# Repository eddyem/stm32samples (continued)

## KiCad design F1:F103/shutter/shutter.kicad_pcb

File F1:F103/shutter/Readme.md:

Shutter control 
===============

Works with bi-stable shutter. 
You can find the device in `/dev/shutterX` (symlink to `/dev/ttyUSBX`).

After powered on, the device will try to close shutter (during one second). 

The CCD (or manual) controlled input allows to open/close shutter by changing its level (depending on `ccdactive` parameter). 
If current configuration can't open or close the shutter immediately, it will be opened/closed as soon as possible, while the input holds its level.

When the shutter is closed, the device will send over USB a message like
```
exptime=10000
shutter=closed
```
with calculated value of opened time and current shutter state. 
If the error occured and shutter can't be closed, user will read `exp=cantclose`, shutter will come into error state. You should close the shutter by external command in that case.

After the shutter completely opened, user can read a message `shutter=opened`.

## Pinout

**PB0** (pullup in) - hall (or reed switch) sensor input (active low) - opened shutter detector

**PB11** (pullup in) - CCD or button input: open at low signal, close at high

**PA3** (ADC in) - shutter voltage (approx 1/12 U)

**PA5** (PP out) - TLE5205 IN2

**PA6** (PP out) - TLE5205 IN1

**PA7** (pullup in) - TLE5205 FB

**PA10** (PP out) - USB pullup (active low)

**PA11**, **PA12** - USB

**PA13**, **PA14** - SWD

## Commands

###    debugging options:
* '0' - shutter OPE
* '1' - shutter CLO
* '2' - shutter OFF
* '3' - shutter HIZ
* 'W' - test watchdog

###    configuration:
* '< n' - voltage on discharged capacitor (*100)
* '> n' - voltage on fully charged capacitor (*100)
* '# n' - duration of electrical pulse to open/close shutter (ms)
* '$ n' - duration of mechanical work to completely open/close shutter (ms)
* '* n' - shutter voltage multiplier
* '/ n' - shutter voltage divider (V=Vadc*M/D)
* 'c n' - open shutter when CCD ext level is n (0/1)
* 'd' - dump current config
* 'e' - erase flash storage
* 'h n' - shutter is opened when hall level is n (0/1)
* 's' - save configuration into flash

###    common control:
* 'A' - get raw ADC values
* 'C' - close shutter / abort exposition
* 'E n' - expose for n milliseconds
* 'O' - open shutter
* 'R' - software reset
* 'S' - get shutter state; also hall and ccd inputs state (1 - active)
* 't' - get MCU temperature (/10degC)
* 'T' - get Tms
* 'v' - get Vdd (/100V)
* 'V' - get shutter voltage (/100V)

Any wrong long message will echo back. Any wrong short command will show help list.

## Shutter control
Commands '0' ...  '3' should be used only for debugging purposes.
To open/close shutter use only 'O', 'C' and 'E' commands.

When opening or closing shutter you will first receive an answer: `OK` if command could be done or `ERR` if there's insufficient voltage on capacitor or shutter is absent.
After opened the message `shutter=opened` will appear. After closing you will receive messages `exptime=xxx` (when `xxx` is approx. exp. time in milliseconds) and `shutter=closed`.

Command 'E' could return `OK`, `ERR` or `ERRNUM`/`I32OVERFLOW` in wrong number format (number could be decimal, 0x.. - hexadecimal, b.. - binary or 0.. - octal).
"Status" command in this case will return `shutter=exposing` and `expfor=xxx` - the given exposition time.

When exposition starts you will receive message `OK` and `shutter=opened`. After its end you'll got `exptime=...`, `shutter=closed`.
If shutter can't be closed, you will give a lots of `exp=cantclose` and different error messages until problem be solved. To stop this error messages give command 'O'.

## Different commands
* 'A' will show raw values for all ADC channels: 0. - capacitor voltage, 1 - MCU temperature, 2 - MCU Vdd. You will give messages like `adcX=val`.

* 't' - `mcut=val`, where val = T*10 degrC.

* 'T' - `tms=val`, val in ms.

* 'v' - `vdd=val`, val in V*100

* 'V' - `voltage=val`, val in V*100

* 'S' - several answers:
  * `shutter=`: `closed`, `opened`, `error`, `process`, `wait` or `exposing` - shutter state 
  * `expfor=...` (only when exposing by command Exxx) - show given exposition time
  * `exptime=...` (only when shutter is opened) - show time since opening
  * `regstate=`: `open`, `close`, `off` or `hiZ` - TLE5205 outputs state
  * `fbstate=`: `0` or `1` - TLE5205 FB out state (1 - error: insufficient voltage or shutter absent)
  * `hall=`: `0` or `1` - 1 for opened shutter, 0 for closed
  * `ccd=`: `0` or `1` - 1 for active (closed contacts) state of "CCD" input

## Configuration
All configuration stored in MCU flash memory, to dump current config just enter command 'd' and you will give an answer like
```
userconf_sz=16
ccdactive=1
hallactive=0
minvoltage=400
workvoltage=700
shuttertime=20
waitingtime=30
shtrvmul=143
shtrvdiv=25
```

* `userconf_sz` - "magick" number to determine first non-empty record in flash storage. The aligned size of one record in bytes.
* `ccdactive` - is level of 'CCD' input to open shutter (1 to open on high and 0 to open on low signal), change this value with command `c`.
* `hallactive` - the same for Hall sensor or reed switch mounted on shutter to indicate opened state, change with `h`.
* `minvoltage` - voltage level on discharged capacitor (V*100 Volts), when shutter is in opened/closed state, the power will be off from coils reaching this level. Can be from 1V to 10V. Change with `<`.
* `workvoltage` - minimal level (V*100 Volts) of charged capacitor to start process of opening/closing, you can open/close shutter only with higher voltage. Can be from 5V to 100V. Change with `>`.
* `shuttertime` - maximal time (milliseconds) of holding active voltage on shutter's coils. Can be from 5ms to 1s. Change with `#`.
* `waitingtime` - waiting time for the shutter to finish its job. The expose time can't be less than this value. Can be from 5ms to 1s. Change with `$`.
* `shtrvmul` - multiplier to calculate capacitor voltage from voltage on ADC input of MCU. Vcap = V*shtrvmul/shtrvdiv. Can be from 1 to 65535. Change with `*`.
* `shtrvdiv` - divider of capacitor voltage calculation. Can be from 1 to 65535. Change with `/`.

All changes of configuration processed in RAM and acts immediately after changed. If you want to store changes, use command `s`.

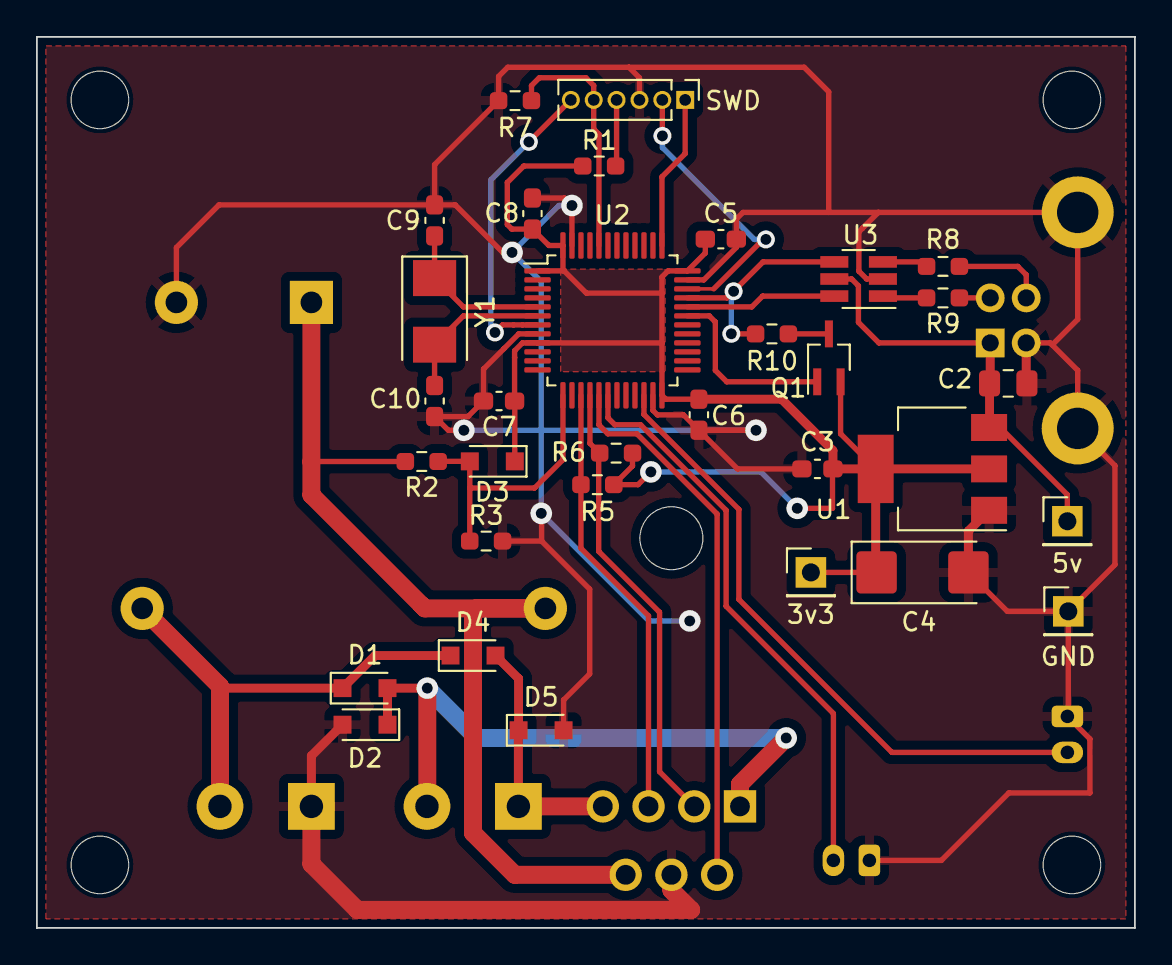
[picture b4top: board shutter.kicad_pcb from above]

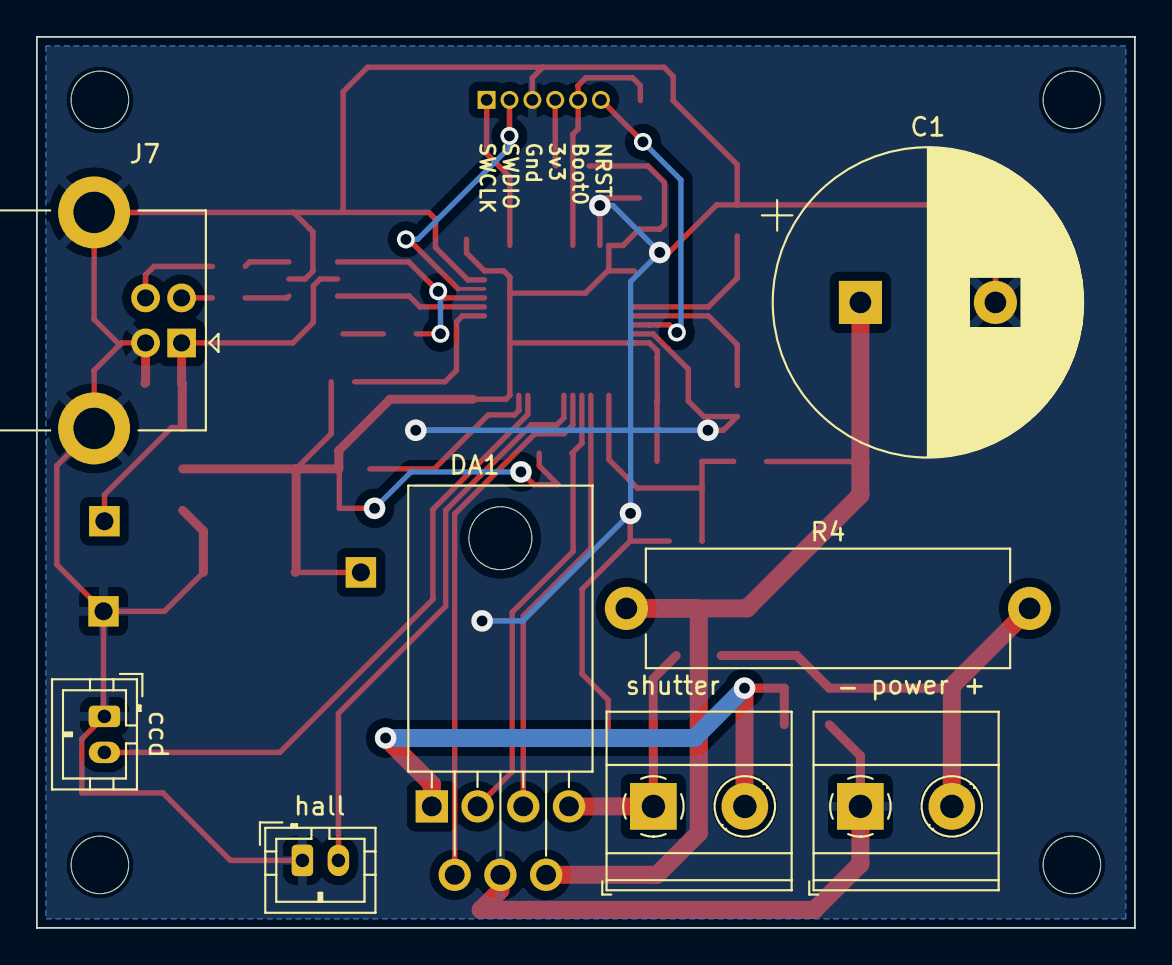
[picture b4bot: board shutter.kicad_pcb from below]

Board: 2 copper layers, 61.0 x 49.5 mm, 44 parts (8 on the bottom side), 28 nets.

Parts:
C1: 2200u, 40V; CP_Radial_D17.0mm_P7.50mm
C2: 1u; C_0805_2012Metric_Pad1.18x1.45mm_HandSolder
C3, C5, C6, C7, C8: 0.1; C_0603_1608Metric_Pad1.08x0.95mm_HandSolder
C4: 47u; CP_EIA-6032-28_Kemet-C_Pad2.25x2.35mm_HandSolder
C9, C10: 6; C_0603_1608Metric_Pad1.08x0.95mm_HandSolder
D1, D2, D3, D4, D5: 1N5819; D_SOD-323_HandSoldering
DA1: TLE5205; TO-220-7_P2.54x3.8mm_StaggerEven_Lead5.85mm_TabDown
H1, H2, H3, H4: MountingHole; MountingHole_3.2mm_M3
J1: shutter; TerminalBlock_Phoenix_MKDS-1,5-2-5.08_1x02_P5.08mm_Horizont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
J2: power; TerminalBlock_Phoenix_MKDS-1,5-2-5.08_1x02_P5.08mm_Horizont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
J3: SWD; PinHeader_1x06_P1.27mm_Vertical
J4: 5v; PinHeader_1x01_P2.54mm_Vertical
J5: GND; PinHeader_1x01_P2.54mm_Vertical
J6: 3v3; PinHeader_1x01_P2.54mm_Vertical
J7: USB_B; USB_B_Lumberg_2411_02_Horizontal
J8: hall; JST_PH_B2B-PH-K_1x02_P2.00mm_Vertical
J9: ccd; JST_PH_B2B-PH-K_1x02_P2.00mm_Vertical
Q1: DTA114Y; SOT-323_SC-70_Handsoldering
R1: 6.9; R_0603_1608Metric_Pad0.98x0.95mm_HandSolder
R2: 56k; R_0603_1608Metric_Pad0.98x0.95mm_HandSolder
R3, R5, R6: 4k7; R_0603_1608Metric_Pad0.98x0.95mm_HandSolder
R4: 300 II; R_Axial_Power_L20.0mm_W6.4mm_P22.40mm
R7: 10k; R_0603_1608Metric_Pad0.98x0.95mm_HandSolder
R8, R9: 22; R_0603_1608Metric_Pad0.98x0.95mm_HandSolder
R10: 1k5; R_0603_1608Metric_Pad0.98x0.95mm_HandSolder
U1: LM1117-3.3; SOT-223-3_TabPin2
U2: STM32F103C6Tx; LQFP-48_7x7mm_P0.5mm
U3: USBLC6-2SC6; SOT-23-6_Handsoldering
Y1: NX5032GA-8MHz; Crystal_SMD_5032-2Pin_5.0x3.2mm

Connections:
+3V3: C3.1, C4.1, C5.1, C6.1, C7.1, C8.1, D3.1 (K), J6.1, Q1.2 (E), R1.1, R5.2, R6.2, U1.2 (VO), U2.1 (VBAT), U2.9 (VDDA), U2.24 (VDD), U2.36 (VDD), U2.48 (VDD)
/BOOT0: J3.5, R7.1, U2.44 (BOOT0)
/NRST: J3.6, U2.7 (NRST)
/OSC_IN: C9.1, U2.5 (PD0), Y1.1
/OSC_OUT: C10.1, U2.6 (PD1), Y1.2
/SHTR_A: DA1.3 (IN1), R6.1, U2.16 (PA6)
/SHTR_B: DA1.5 (IN2), R5.1, U2.15 (PA5)
/SHTR_FB: DA1.2 (EF), U2.17 (PA7)
/SHTR_V: D3.2 (A), R2.2, R3.1, U2.13 (PA3)
/SWCLK: J3.1, U2.37 (PA14)
/SWDIO: J3.2, U2.34 (PA13)
/USBDM: U2.32 (PA11), U3.6 (I/O1)
/USBDP: R10.1, U2.33 (PA12), U3.4 (I/O2)
/USB_PU: Q1.1 (B), U2.31 (PA10)
/Uin: D1.1 (K), D4.1 (K), J2.2, R4.1
/VBUS: C2.1, J4.1, J7.1 (VBUS), U1.3 (VI), U3.5 (VBUS)
GND: C1.2, C2.2, C3.2, C4.2, C5.2, C6.2, C7.2, C8.2, C9.2, C10.2, D2.2 (A), D5.2 (A), DA1.4 (GND), J2.1, J3.3, J5.1, J7.4 (GND), J7.5 (Shield), J8.1, J9.1, R3.2, R7.2, U1.1 (GND), U2.8 (VSSA), U2.23 (VSS), U2.35 (VSS), U2.47 (VSS), U3.2 (GND)
unnamed: D1.2 (A), D2.1 (K), DA1.1 (OUT1), J1.2
unnamed: D4.2 (A), D5.1 (K), DA1.7 (OUT2), J1.1
unnamed: C1.1, DA1.6 (Vs), R2.1, R4.2
unnamed: J3.4, R1.2
unnamed: J7.3 (D+), R8.1
unnamed: J7.2 (D-), R9.1
unnamed: J8.2, U2.18 (PB0)
unnamed: J9.2, U2.22 (PB11)
unnamed: Q1.3 (C), R10.2
unnamed: R8.2, U3.3 (I/O2)
unnamed: R9.2, U3.1 (I/O1)

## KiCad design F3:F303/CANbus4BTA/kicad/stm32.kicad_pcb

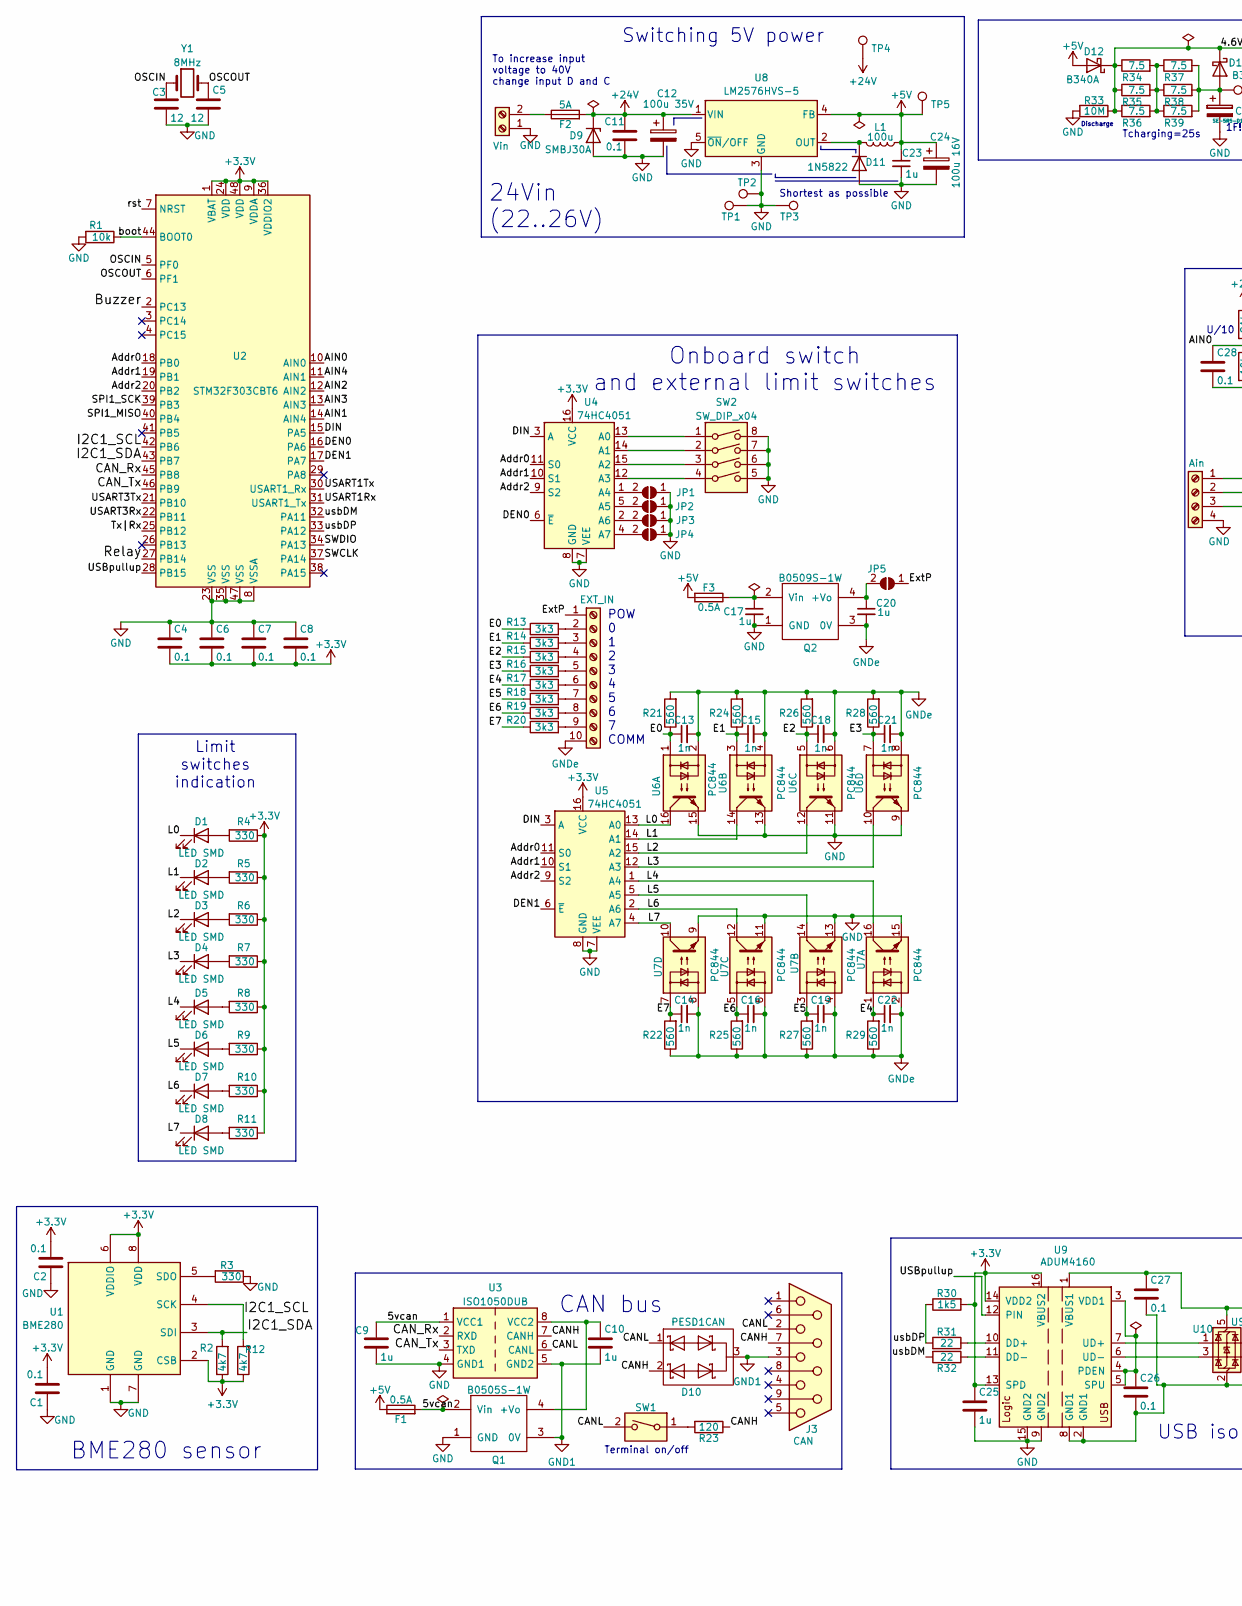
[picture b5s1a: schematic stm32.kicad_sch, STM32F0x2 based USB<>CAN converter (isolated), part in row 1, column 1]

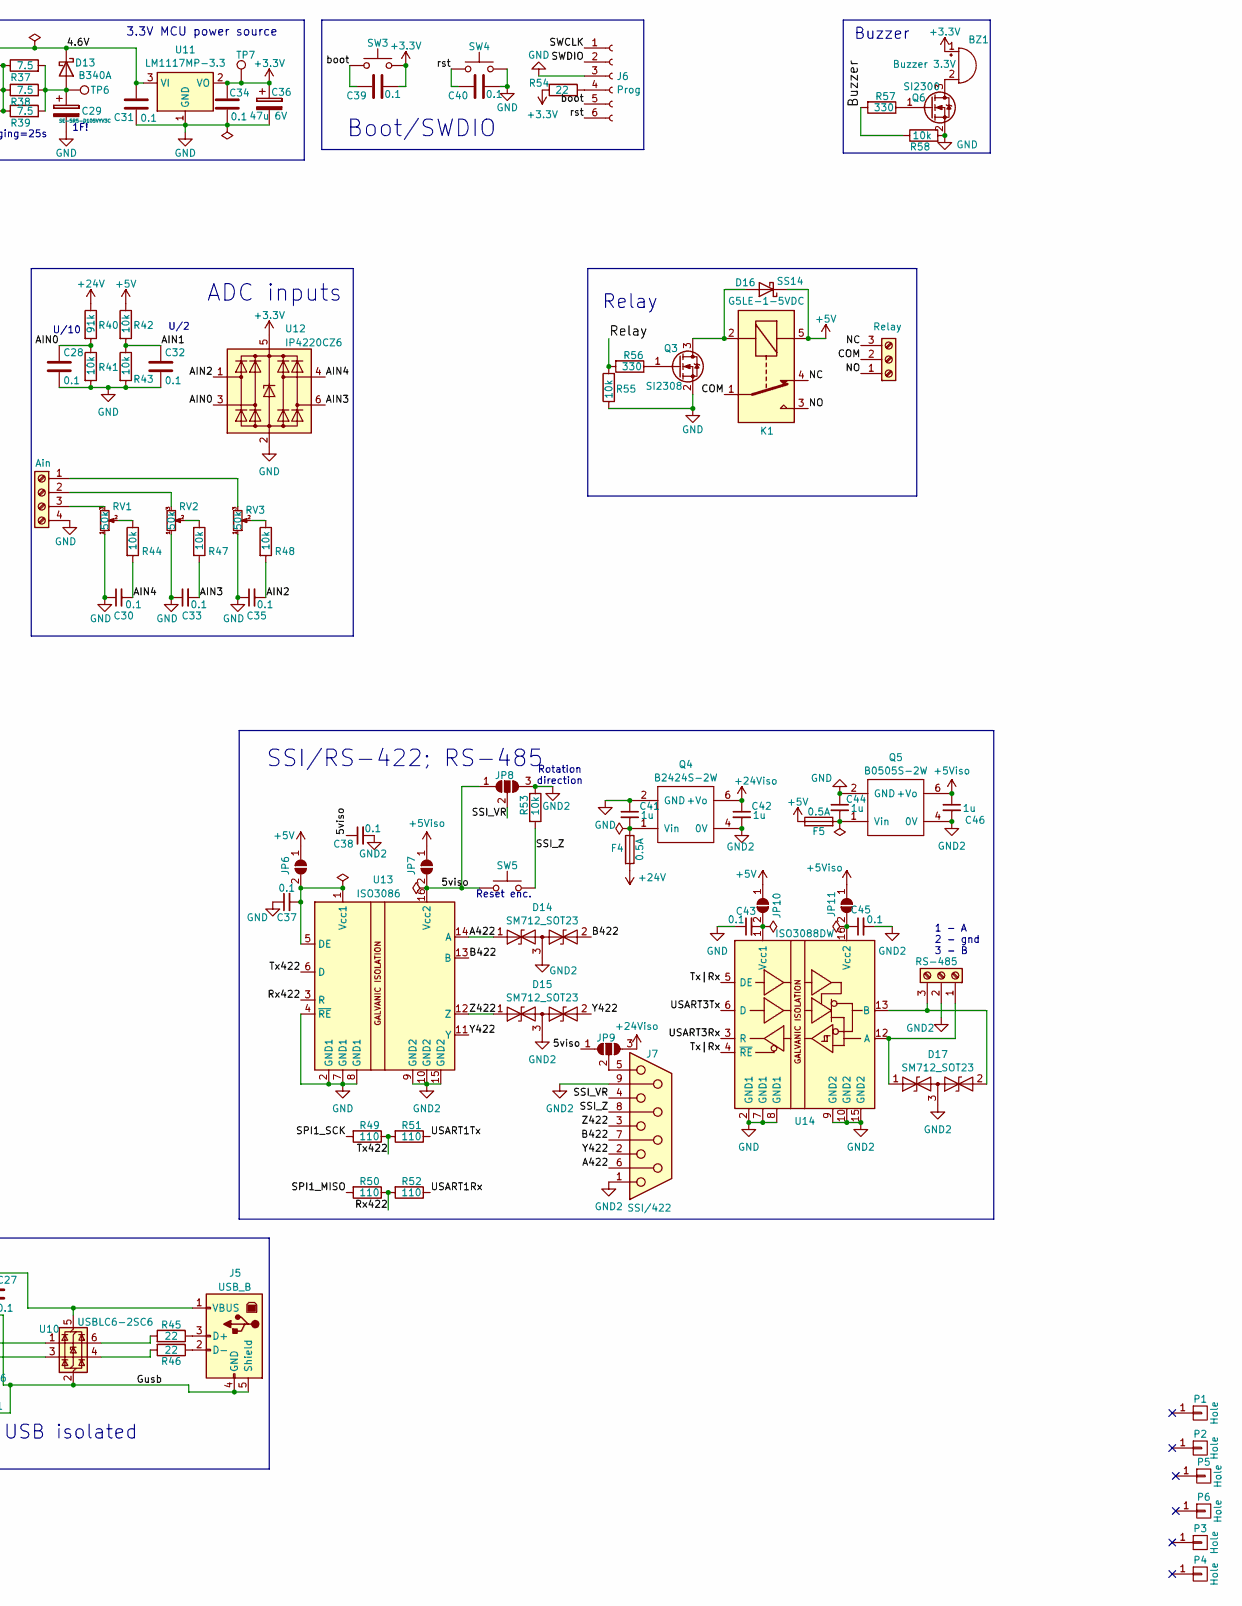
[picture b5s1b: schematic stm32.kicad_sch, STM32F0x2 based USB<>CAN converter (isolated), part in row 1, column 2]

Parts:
BZ1: Buzzer 3.3V; Buzzer_12x9.5RM7.6
C1, C2, C4, C6, C7, C8, C11, C26, C27, C28, C30, C31, C32, C33, C34, C35, C37, C38, C39, C40, C43, C45: 0.1; C_0603_1608Metric_Pad1.08x0.95mm_HandSolder
C3, C5: 12; C_0603_1608Metric_Pad1.08x0.95mm_HandSolder
C9, C10, C17, C20, C23, C25, C41, C42, C44, C46: 1u; C_0805_2012Metric_Pad1.18x1.45mm_HandSolder
C12: 100u 35V; CP_Radial_D8.0mm_P3.50mm
C13, C14, C15, C16, C18, C19, C21, C22: 1n; C_0603_1608Metric_Pad1.08x0.95mm_HandSolder
C24: 100u 16V; CP_Radial_D8.0mm_P3.50mm
C29: SE-5R5-D105VYV3C; DX_5R5VxxxxU_D19.0mm_P5.00mm
C36: 47u 6V; CP_EIA-3216-18_Kemet-A_Pad1.58x1.35mm_HandSolder
D1, D2, D3, D4, D5, D6, D7, D8: LED SMD; LED_0805_2012Metric_Pad1.15x1.40mm_HandSolder
D9: SMBJ30A; D_SMB-SMC_Universal_Handsoldering
D10: PESD1CAN; SOT-23
D11: 1N5822; D_DO-201_P3.81mm_Vertical_AnodeUp
D12, D13: B340A; D_SMA-SMB_Universal_Handsoldering
D14, D15, D17: SM712_SOT23; SOT-23
D16: SS14; D_SMA-SMB_Universal_Handsoldering
F1, F3, F4, F5: 0.5A; Fuse_1206_3216Metric
F2: 5A; Fuse_1206_3216Metric
J1: Vin; TerminalBlock_Phoenix_MKDS-1,5-2_1x02_P5.00mm_Horizontal
J2: EXT_IN; PhoenixContact_MC_1,5_10-GF-5.08_1x10_P5.08mm_Horizontal_Th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
J3: CAN; DSUB-9_Female_Horizontal_P2.77x2.84mm_EdgePinOffset4.94mm_H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
J4: Ain; TerminalBlock_Phoenix_MKDS-1,5-4_1x04_P5.00mm_Horizontal
J5: USB_B; USB_B_OST_USB-B1HSxx_Horizontal
J6: Prog; PinSocket_1x06_P1.27mm_Vertical
J7: SSI/422; DSUB-9_Female_Horizontal_P2.77x2.84mm_EdgePinOffset4.94mm_H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
J8: Relay; TerminalBlock_Phoenix_MKDS-1,5-3_1x03_P5.00mm_Horizontal
J9: RS-485; TerminalBlock_Phoenix_MKDS-1,5-3_1x03_P5.00mm_Horizontal
JP1, JP2, JP3, JP4, JP5, JP6, JP7, JP10, JP11: SolderJumper_2_Open; SolderJumper-2_P1.3mm_Open_TrianglePad1.0x1.5mm
JP8, JP9: 3; SolderJumper-3_P2.0mm_Open_TrianglePad1.0x1.5mm
K1: G5LE-1-5VDC; Relay_SPDT_Omron-G5LE-1
L1: 100u; L_Toroid_Horizontal_D6.5mm_P10.00mm_Diameter7-5mm_Amidon-T25
P1, P2, P3, P4, P5, P6: Hole; Hole_3mm
Q1: B0505S-1W; B0x0xS
Q2: B0509S-1W; B0x0xS
Q3: SI2308; SOT-23_Handsoldering
Q4: B2424S-2W; B0505S-2W
Q5: B0505S-2W
Q6: SI2300; SOT-23_Handsoldering
R1, R41, R42, R43, R44, R47, R48, R53, R55, R58: 10k; R_0603_1608Metric_Pad0.98x0.95mm_HandSolder
R2, R12: 4k7; R_0603_1608Metric_Pad0.98x0.95mm_HandSolder
R3, R4, R5, R6, R7, R8, R9, R10, R11, R56, R57: 330; R_0603_1608Metric_Pad0.98x0.95mm_HandSolder
R13, R14, R15, R16, R17, R18, R19, R20: 3k3; R_2010_5025Metric_Pad1.40x2.65mm_HandSolder
R21, R22, R24, R25, R26, R27, R28, R29: 560; R_0603_1608Metric_Pad0.98x0.95mm_HandSolder
R23: 120; R_1210_3225Metric_Pad1.30x2.65mm_HandSolder
R30: 1k5; R_0603_1608Metric_Pad0.98x0.95mm_HandSolder
R31, R32, R45, R46, R54: 22; R_0603_1608Metric_Pad0.98x0.95mm_HandSolder
R33: 10M; R_0603_1608Metric_Pad0.98x0.95mm_HandSolder
R34, R35, R36, R37, R38, R39: 7.5; R_2010_5025Metric_Pad1.40x2.65mm_HandSolder
R40: 91k; R_0603_1608Metric_Pad0.98x0.95mm_HandSolder
R49, R50, R51, R52: 110; R_0603_1608Metric_Pad0.98x0.95mm_HandSolder
RV1, RV2, RV3: 50k; Potentiometer_Bourns_3296W_Vertical
SW1: SW_DIP_x01; SW_DIP_SPSTx01_Slide_6.7x4.1mm_W7.62mm_P2.54mm_LowProfile
SW2: SW_DIP_x04; SW_DIP_SPSTx04_Slide_9.78x12.34mm_W7.62mm_P2.54mm
SW3, SW4, SW5: SW_Push; SW_SPST_FSMSM
TP1, TP2, TP3: Gnd; PinSocket_1x01_P2.54mm_Vertical
TP4: 24V; PinSocket_1x01_P2.54mm_Vertical
TP5: 5V; PinSocket_1x01_P2.54mm_Vertical
TP6: 4.6V; PinSocket_1x01_P2.54mm_Vertical
TP7: 3.3V; PinSocket_1x01_P2.54mm_Vertical
U1: BME280; Bosch_LGA-8_2.5x2.5mm_P0.65mm_ClockwisePinNumbering
U2: STM32F303CBT6; LQFP-48_7x7mm_P0.5mm
U3: ISO1050DUB; SOP-8_6.62x9.15mm_P2.54mm
U4, U5: 74HC4051; SOIC-16_3.9x9.9mm_P1.27mm
U6, U7: PC844; DIP-16_W7.62mm
U8: LM2576HVS-5; TO-263-5_TabPin3
U9: ADUM4160; SOIC-16W_7.5x10.3mm_P1.27mm
U10: USBLC6-2SC6; SOT-23-6
U11: LM1117MP-3.3; SOT-223-3_TabPin2
U12: IP4220CZ6; SOT-23-6
U13: ISO3086; SOIC-16W_7.5x10.3mm_P1.27mm
U14: ISO3088DW; SOIC-16W_7.5x10.3mm_P1.27mm
Y1: 8MHz; Crystal_HC49-U_Vertical

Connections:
+3.3V: BZ1.1 (-), C1.2, C2.2, C4.2, C6.2, C7.2, C8.2, C25.1, C34.1, C36.1, C39.2, R2.1, R4.1, R5.1, R6.1, R7.1, R8.1, R9.1, R10.1, R11.1, R12.1, R30.2, R54.2, SW3.2, TP7.1, U1.2 (CSB), U1.6 (VDDIO), U1.8 (VDD), U2.1 (VBAT), U2.9 (VDDA), U2.24 (VDD), U2.36 (VDDIO2), U2.48 (VDD), U4.16 (VCC), U5.16 (VCC), U9.13 (SPD), U9.14 (VDD2), U9.16 (VBUS2), U11.2 (VO), U12.5 (VBUS)
+5V: C23.1, C24.1, D12.2 (A), D16.1 (K), F1.1, F3.2, F5.1, JP6.1 (A), JP10.1 (A), K1.5, L1.1, R42.1, TP5.1, U8.4 (FB)
+5Viso: C46.1, JP7.1 (A), JP11.1 (A), Q5.6 (+Vo)
+24V: C11.1, C12.1, D9.1 (K), F2.2, F4.2, R40.1, TP4.1, U8.1 (VIN)
+24Viso: C42.1, JP9.3 (B), Q4.6 (+Vo)
/4.6V: C31.1, D12.1 (K), D13.1 (K), R33.1, R34.1, R35.1, R36.1, U11.3 (VI)
/5vcan: C9.1, F1.2, Q1.2 (Vin), U3.1 (VCC1)
/5viso: C38.1, JP7.2 (B), JP8.1 (A), JP9.1 (A), SW5.1, U13.16 (Vcc2)
/A422: D14.1 (A1), J7.6, U13.14 (A)
/AIN0: C28.1, R40.2, R41.1, U2.10 (AIN0), U12.3 (I/O2)
/AIN1: C32.1, R42.2, R43.1, U2.14 (AIN4)
/AIN2: C35.2, R48.2, U2.12 (AIN2), U12.1 (I/O1)
/AIN3: C33.2, R47.2, U2.13 (AIN3), U12.6 (I/O4)
/AIN4: C30.2, R44.2, U2.11 (AIN1), U12.4 (I/O3)
/Addr0: U2.18 (PB0), U4.11 (S0), U5.11 (S0)
/Addr1: U2.19 (PB1), U4.10 (S1), U5.10 (S1)
/Addr2: U2.20 (PB2), U4.9 (S2), U5.9 (S2)
/B422: D14.2 (A2), J7.7, U13.13 (B)
/Buzzer: R57.2, R58.1, U2.2 (PC13)
/CANH: D10.2 (K), J3.7, R23.1, U3.7 (CANH)
/CANL: D10.1 (K), J3.2, SW1.2, U3.6 (CANL)
/CAN_Rx: U2.45 (PB8), U3.2 (RXD)
/CAN_Tx: U2.46 (PB9), U3.3 (TXD)
/COM: J8.2, K1.1
/DEN0: U2.16 (PA6), U4.6 (~E)
/DEN1: U2.17 (PA7), U5.6 (~E)
/DIN: U2.15 (PA5), U4.3 (A), U5.3 (A)
/E0: C13.1, R13.1, R21.1, U6.1
/E1: C15.1, R14.1, R24.1, U6.3
/E2: C18.1, R15.1, R26.1, U6.5
/E3: C21.1, R16.1, R28.1, U6.7
/E4: C22.1, R17.1, R29.2, U7.1
/E5: C19.1, R18.1, R27.2, U7.3
/E6: C16.1, R19.1, R25.2, U7.5
/E7: C14.1, R20.1, R22.2, U7.7
/ExtP: J2.1, JP5.1 (A)
/Gusb: C26.2, C27.2, J5.4 (GND), J5.5 (Shield), U9.2 (GND1), U9.8 (GND1), U10.2 (GND)
/I2C1_SCL: R12.2, U1.4 (SCK), U2.42 (PB6)
/I2C1_SDA: R2.2, U1.3 (SDI), U2.43 (PB7)
/L0: D1.1 (K), U5.13 (A0), U6.16
/L1: D2.1 (K), U5.14 (A1), U6.14
/L2: D3.1 (K), U5.15 (A2), U6.12
/L3: D4.1 (K), U5.12 (A3), U6.10
/L4: D5.1 (K), U5.1 (A4), U7.16
/L5: D6.1 (K), U5.5 (A5), U7.14
/L6: D7.1 (K), U5.2 (A6), U7.12
/L7: D8.1 (K), U5.4 (A7), U7.10
/NC: J8.3, K1.4
/NO: J8.1, K1.3
/OSCIN: C3.1, U2.5 (PF0), Y1.1
/OSCOUT: C5.1, U2.6 (PF1), Y1.2
/Relay: R55.2, R56.2, U2.27 (PB14)
/Rx422: R50.1, R52.2, U13.3 (R)
/SPI1_MISO: R50.2, U2.40 (PB4)
/SPI1_SCK: R49.2, U2.39 (PB3)
/SSI_VR: J7.4, JP8.2 (C)
/SSI_Z: J7.8, R53.2, SW5.2
/SWCLK: J6.1, U2.37 (PA14)
/SWDIO: J6.2, U2.34 (PA13)
/Tx422: R49.1, R51.2, U13.6 (D)
/Tx|Rx: U2.25 (PB12), U14.4 (~RE), U14.5 (DE)
/USART1Rx: R52.1, U2.31 (USART1_Tx)
/USART1Tx: R51.1, U2.30 (USART1_Rx)
/USART3Rx: U2.22 (PB11), U14.3 (R)
/USART3Tx: U2.21 (PB10), U14.6 (D)
/USBpullup: U2.28 (PB15), U9.12 (PIN)
/Y422: D15.2 (A2), J7.2, U13.11 (Y)
/Z422: D15.1 (A1), J7.3, U13.12 (Z)
/boot: C39.1, J6.5, R1.1, SW3.1, U2.44 (BOOT0)
/rst: C40.1, J6.6, SW4.1, U2.7 (NRST)
/usbDM: R32.2, U2.32 (PA11)
/usbDP: R30.1, R31.2, U2.33 (PA12)
GND: C1.1, C2.1, C3.2, C4.1, C5.2, C6.1, C7.1, C8.1, C9.2, C11.2, C12.2, C17.2, C23.2, C24.2, C25.2, C28.2, C29.2, C30.1, C31.2, C32.2, C33.1, C34.2, C35.1, C36.2, C37.1, C40.2, C41.1, C43.1, C44.1, D9.2 (A), D11.2 (A), J1.1, J4.4, J6.3, JP1.1 (A), JP2.1 (A), JP3.1 (A), JP4.1 (A), Q1.1 (GND), Q2.1 (GND), Q3.2 (S), Q4.2 (GND), Q5.2 (GND), Q6.2 (S), R1.2, R3.1, R33.2, R41.2, R43.2, R55.1, R58.2, RV1.1, RV2.1, RV3.1, SW2.5, SW2.6, SW2.7, SW2.8, SW4.2, TP1.1, TP2.1, TP3.1, U1.1 (GND), U1.7 (GND), U2.8 (VSSA), U2.23 (VSS), U2.35 (VSS), U2.47 (VSS), U3.4 (GND1), U4.7 (VEE), U4.8 (GND), U5.7 (VEE), U5.8 (GND), U6.9, U6.11, U6.13, U6.15, U7.9, U7.11, U7.13, U7.15, U8.3 (GND), U8.5 (~ON/OFF), U9.9 (GND2), U9.15 (GND2), U11.1 (GND), U12.2 (GND), U13.2 (GND1), U13.4 (~RE), U13.7 (GND1), U13.8 (GND1), U14.2 (GND1), U14.7 (GND1), U14.8 (GND1)
GND1: C10.2, D10.3 (O), J3.3, Q1.3 (0V), U3.5 (GND2)
GND2: C38.2, C42.2, C45.2, C46.2, D14.3 (common), D15.3 (common), D17.3 (common), J7.1, J7.9, J9.2, JP8.3 (B), Q4.4 (0V), Q5.4 (0V), R53.1, U13.9 (GND2), U13.10 (GND2), U13.15 (GND2), U14.9 (GND2), U14.10 (GND2), U14.15 (GND2)
GNDe: C13.2, C14.2, C15.2, C16.2, C18.2, C19.2, C20.2, C21.2, C22.2, J2.10, Q2.3 (0V), R21.2, R22.1, R24.2, R25.1, R26.2, R27.1, R28.2, R29.1, U6.2, U6.4, U6.6, U6.8, U7.2, U7.4, U7.6, U7.8
unnamed: BZ1.2 (+), Q6.3 (D)
unnamed: D1.2 (A), R4.2
unnamed: D2.2 (A), R5.2
unnamed: D3.2 (A), R6.2
unnamed: D4.2 (A), R7.2
unnamed: D5.2 (A), R8.2
unnamed: D6.2 (A), R9.2
unnamed: D7.2 (A), R10.2
unnamed: D8.2 (A), R11.2
unnamed: D11.1 (K), L1.2, U8.2 (OUT)
unnamed: C29.1, D13.2 (A), R37.2, R38.2, R39.2, TP6.1
unnamed: D16.2 (A), K1.2, Q3.3 (D)
unnamed: D17.1 (A1), J9.1, U14.12 (A)
unnamed: D17.2 (A2), J9.3, U14.13 (B)
unnamed: F2.1, J1.2
unnamed: J2.2, R13.2
unnamed: J2.3, R14.2
unnamed: J2.4, R15.2
unnamed: J2.5, R16.2
unnamed: J2.6, R17.2
unnamed: J2.7, R18.2
unnamed: J2.8, R19.2
unnamed: J2.9, R20.2
unnamed: J4.1, RV3.3
unnamed: J4.2, RV2.3
unnamed: J4.3, RV1.3
unnamed: J5.3 (D+), R45.1
unnamed: J5.2 (D-), R46.1
unnamed: C27.1, J5.1 (VBUS), U9.1 (VBUS1), U10.5 (VBUS)
unnamed: J6.4, R54.1
unnamed: JP1.2 (B), U4.1 (A4)
unnamed: JP2.2 (B), U4.5 (A5)
unnamed: JP3.2 (B), U4.2 (A6)
unnamed: JP4.2 (B), U4.4 (A7)
unnamed: C20.1, JP5.2 (B), Q2.4 (+Vo)
unnamed: C37.2, JP6.2 (B), U13.1 (Vcc1), U13.5 (DE)
unnamed: J7.5, JP9.2 (C)
unnamed: C43.2, JP10.2 (B), U14.1 (Vcc1)
unnamed: C45.1, JP11.2 (B), U14.16 (Vcc2)
unnamed: C10.1, Q1.4 (+Vo), U3.8 (VCC2)
unnamed: C17.1, F3.1, Q2.2 (Vin)
unnamed: Q3.1 (G), R56.1
unnamed: C41.2, F4.1, Q4.1 (Vin)
unnamed: C44.2, F5.2, Q5.1 (Vin)
unnamed: Q6.1 (G), R57.1
unnamed: R23.2, SW1.1
unnamed: R34.2, R35.2, R36.2, R37.1, R38.1, R39.1
unnamed: R44.1, RV1.2
unnamed: R45.2, U10.6 (I/O1)
unnamed: R46.2, U10.4 (I/O2)
unnamed: R47.1, RV2.2
unnamed: R48.1, RV3.2
unnamed: R3.2, U1.5 (SDO)
unnamed: SW2.1, U4.13 (A0)
unnamed: SW2.2, U4.14 (A1)
unnamed: SW2.3, U4.15 (A2)
unnamed: SW2.4, U4.12 (A3)
unnamed: R31.1, U9.10 (DD+)
unnamed: R32.1, U9.11 (DD-)
unnamed: C26.1, U9.3 (VDD1), U9.4 (PDEN), U9.5 (SPU)
unnamed: U9.7 (UD+), U10.1 (I/O1)
unnamed: U9.6 (UD-), U10.3 (I/O2)

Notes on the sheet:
Limit switches indication
U/2
Switching 5V power
POW 0 1 2 3 4 5 6 7 COMM
BME280 sensor
Buzzer
Shortest as possible
CAN bus
U/10
USB isolated
1F!
To increase input voltage to 40V change input D and C
1 - A 2 - gnd 3 - B
Boot/SWDIO
3.3V MCU power source
Rotation direction
24Vin (22..26V)
Tcharging=25s
ADC inputs
Terminal on/off
Discharge
Onboard switch and external limit switches
Relay
Reset enc.
SSI/RS-422; RS-485

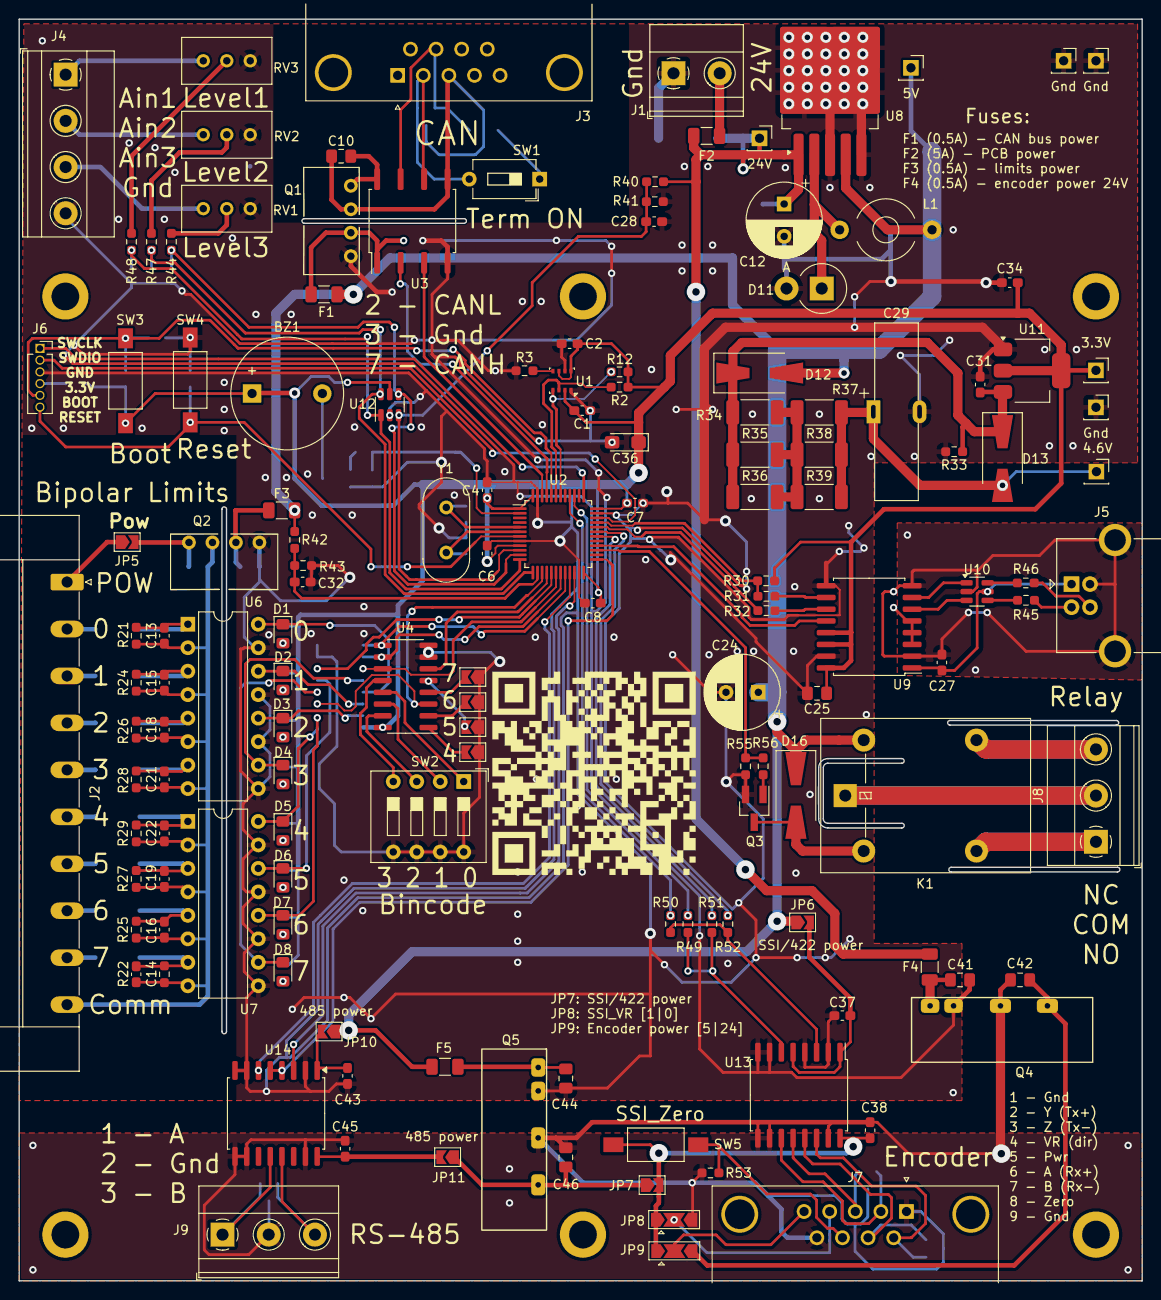
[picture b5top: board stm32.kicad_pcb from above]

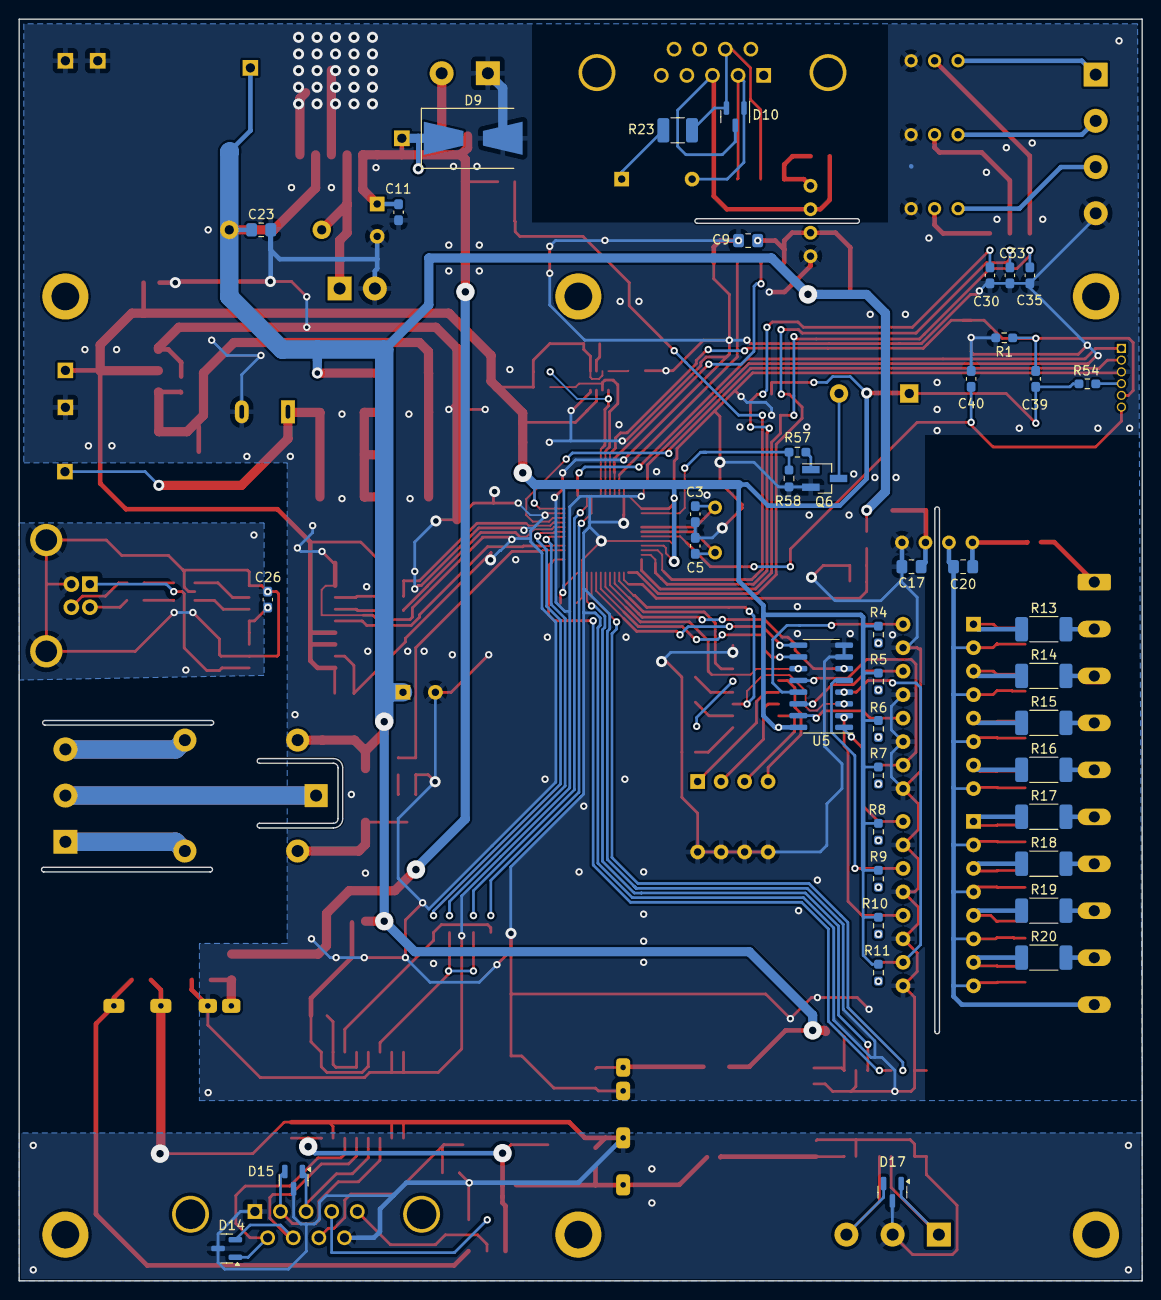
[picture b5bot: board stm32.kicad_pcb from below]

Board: 2 copper layers, 121.5 x 136.5 mm, 191 parts (41 on the bottom side), 138 nets.
